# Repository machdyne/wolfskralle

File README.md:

# Wolfskralle Programmer

Wolfskralle is an ISP + spring contact programmer for CH32 MCUs and [Zwölf](https://github.com/machdyne/zwolf) [LS10](https://machdyne.com/product/zwolf-ls10/) modules.

This repo will contain schematics, pinouts and a 3D-printable socket housing for the spring connector.

Find more information on the [Wolfskralle product page](https://machdyne.com/product/wolfskralle-programmer/).

## Pinout

```
7 5 3 1
8 6 4 2
```

| Pin | Signal |
| --- | ------ |
| 1 | ZP1 (Zwölf GSCL) / SWCLK | 
| 3 | ZP2 (Zwölf GSDA) | 
| 5 | SWIO (programmer swio) | 
| 7 | RESET (programmer reset) | 
| 2 | TPWR3V3 (target power) | 
| 4 | TSWIO (target swio) | 
| 6 | TRESET (target reset) | 
| 8 | GND | 

## Firmware

The Wolfskralle's firmware and its command-line tool, `wolfctl`, are being
written in phases; see [docs/plan.md](docs/plan.md) for the plan and the
current state.

```
$ make -C firmware deps && make -C firmware      # firmware/wolfskralle.bin
$ make -C firmware flash                         # with a WCH-LinkE on J2
$ make -C host && make -C host test              # host/wolfctl, protocol tests
$ host/wolfctl info
$ host/wolfctl flash basic-ls10a.bin             # program the module
```

| Document | Contents |
|---|---|
| [docs/plan.md](docs/plan.md) | development plan and history |
| [docs/hardware.md](docs/hardware.md) | the board as the firmware sees it (pins, v0/v1) |
| [docs/firmware.md](docs/firmware.md) | building and flashing the firmware |
| [docs/protocol.md](docs/protocol.md) | the USB protocol |
| [docs/swio.md](docs/swio.md) | the link to the target: SWIO, its timing, the scan |
| [docs/debug.md](docs/debug.md) | connecting to the chip, identifying and reading it |
| [docs/programming.md](docs/programming.md) | programming a module, and the failsafe rules |
| [docs/sechs.md](docs/sechs.md) | checking a module over Sechs: is BASIC installed and running? |
| [docs/wolfctl.md](docs/wolfctl.md) | the command-line tool |
| [docs/hwtest.md](docs/hwtest.md) | hardware tests and their results |

## License

The contents of this repo are released under the [Lone Dynamics Open License](LICENSE.md).

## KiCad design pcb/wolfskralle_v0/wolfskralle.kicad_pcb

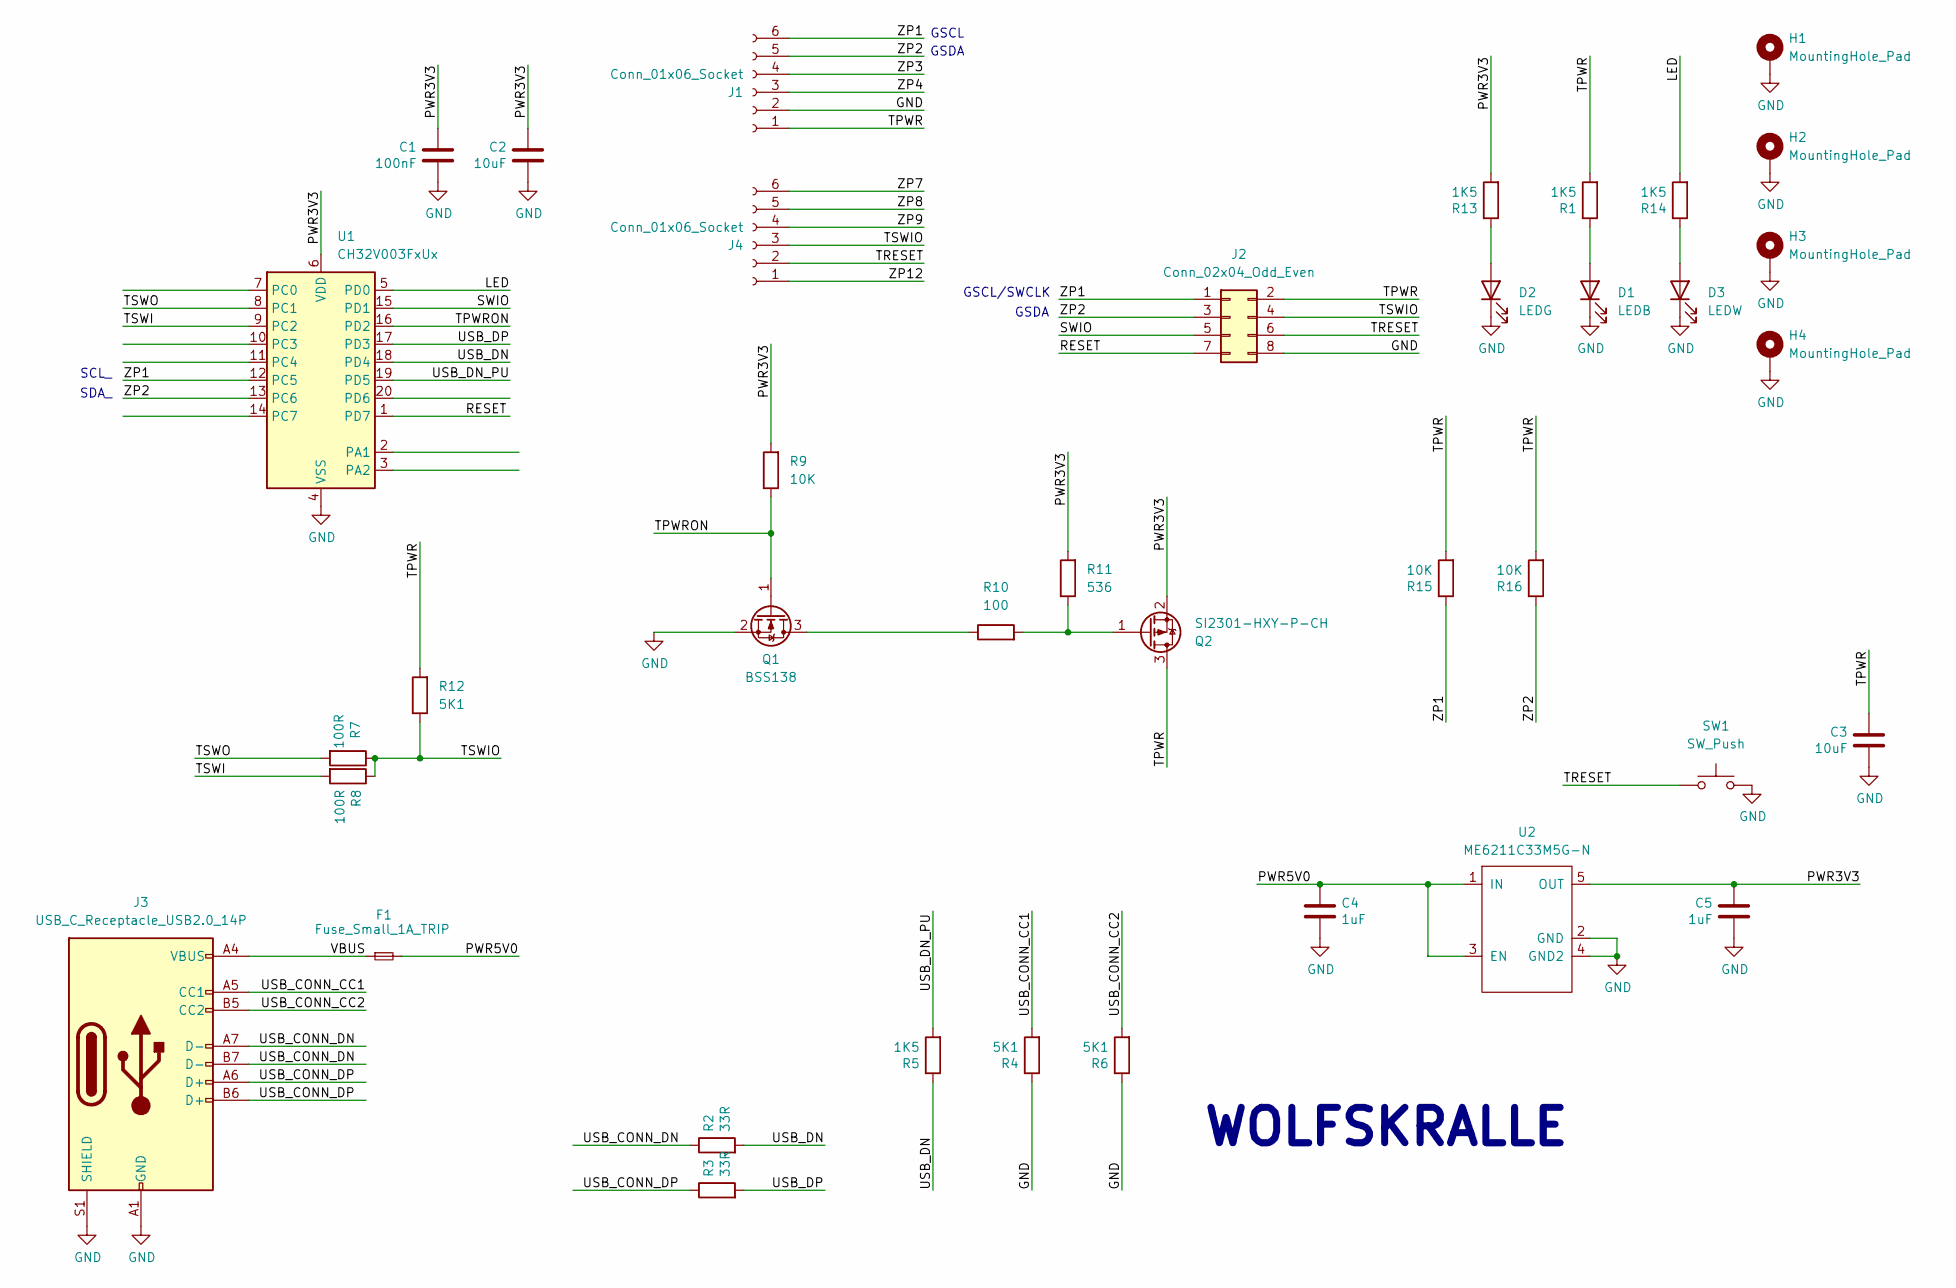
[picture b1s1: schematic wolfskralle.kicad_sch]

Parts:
C1: 100nF; C_0402_1005Metric
C2, C3: 10uF; C_0402_1005Metric
C4, C5: 1uF; C_0402_1005Metric
D1: LEDB; LED_0603_1608Metric
D2: LEDG; LED_0603_1608Metric
D3: LEDW; LED_0603_1608Metric
F1: Fuse_Small_1A_TRIP; Fuse_0603_1608Metric
H1, H2, H3, H4: MountingHole_Pad; MountingHole_2.7mm_M2.5_DIN965_Pad
J1, J4: Conn_01x06_Socket; SPRING-MALE-6P-TIGHTHOLES
J2: Conn_02x04_Odd_Even; PinHeader_2x04_P2.54mm_Horizontal
J3: USB_C_Receptacle_USB2.0_14P; USB_C_Receptacle_HRO_TYPE-C-31-M-12-BIG-PADS-PASTE
Q1: BSS138; SOT-23
Q2: SI2301-HXY-P-CH; SOT-23
R1, R5, R13, R14: 1K5; R_0402_1005Metric
R2, R3: 33R; R_0402_1005Metric
R4, R6, R12: 5K1; R_0402_1005Metric
R7, R8: 100R; R_0402_1005Metric
R9, R15, R16: 10K; R_0402_1005Metric
R10: 100; R_0402_1005Metric
R11: 536; R_0402_1005Metric
SW1: SW_Push; Button_2P_3x4mm
U1: CH32V003FxUx; QFN-20-1EP_3x3mm_P0.4mm_EP1.65x1.65mm
U2: ME6211C33M5G-N; TSOP-5_1.65x3.05mm_P0.95mm

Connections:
/LED: R14.2, U1.5 (PD0)
/PWR3V3: C1.1, C2.1, C5.1, Q2.2 (S), R9.2, R11.2, R13.2, U1.6 (VDD), U2.5 (OUT)
/PWR5V0: C4.1, F1.2, U2.1 (IN), U2.3 (EN)
/RESET: J2.7, U1.1 (PD7)
/SWIO: J2.5, U1.15 (PD1)
/TPWR: C3.1, J1.1, J2.2, Q2.3 (D), R1.2, R12.2, R15.2, R16.2
/TPWRON: Q1.1 (G), R9.1, U1.16 (PD2)
/TRESET: J2.6, J4.2, SW1.1
/TSWI: R8.2, U1.9 (PC2)
/TSWIO: J2.4, J4.3, R7.1, R8.1, R12.1
/TSWO: R7.2, U1.8 (PC1)
/USB_CONN_CC1: J3.A5 (CC1), R4.2
/USB_CONN_CC2: J3.B5 (CC2), R6.2
/USB_CONN_DN: J3.A7 (D-), J3.B7 (D-), R2.1
/USB_CONN_DP: J3.A6 (D+), J3.B6 (D+), R3.1
/USB_DN: R2.2, R5.1, U1.18 (PD4)
/USB_DN_PU: R5.2, U1.19 (PD5)
/USB_DP: R3.2, U1.17 (PD3)
/VBUS: F1.1, J3.A4 (VBUS), J3.A9 (VBUS), J3.B4 (VBUS), J3.B9 (VBUS)
/ZP1: J1.6, J2.1, R15.1, U1.12 (PC5)
/ZP2: J1.5, J2.3, R16.1, U1.13 (PC6)
/ZP3: J1.4
/ZP4: J1.3
/ZP7: J4.6
/ZP8: J4.5
/ZP9: J4.4
/ZP12: J4.1
GND: C1.2, C2.2, C3.2, C4.2, C5.2, D1.1 (K), D2.1 (K), D3.1 (K), H1.1, H2.1, H3.1, H4.1, J1.2, J2.8, J3.A1 (GND), J3.A12 (GND), J3.B1 (GND), J3.B12 (GND), J3.S1 (SHIELD), Q1.2 (S), R4.1, R6.1, SW1.2, U1.4 (VSS), U1.21 (VSS), U2.2 (GND), U2.4 (GND2)
unnamed: D1.2 (A), R1.1
unnamed: D2.2 (A), R13.1
unnamed: D3.2 (A), R14.1
unnamed: Q1.3 (D), R10.1
unnamed: Q2.1 (G), R10.2, R11.1

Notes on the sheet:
GSCL
GSDA
SCL_
GSCL/SWCLK
WOLFSKRALLE
SDA_

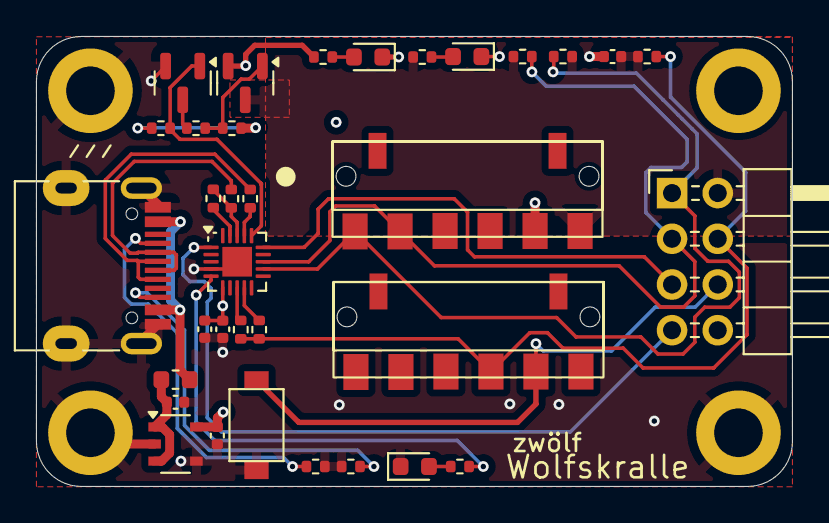
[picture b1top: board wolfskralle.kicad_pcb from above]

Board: 2 copper layers, 42.0 x 25.0 mm, 38 parts (0 on the bottom side), 27 nets.

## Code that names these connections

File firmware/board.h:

/*
 * Wolfskralle board definitions. See docs/hardware.md.
 *
 * Build for v0 (default) or v1:  make BOARD=v1
 */

#ifndef BOARD_H
#define BOARD_H

#include "wkproto.h"

#if defined(BOARD_V1)
#define BOARD_ID        WK_BOARD_V1
#else
#define BOARD_V0        1
#define BOARD_ID        WK_BOARD_V0
/* the watchdog: feeds it (main loop, every SWIO packet, long waits) */
#define WDT_FEED()      (IWDG->CTLR = 0xAAAA)

#endif

#define PIN_LED         PD0     /* white LED D3, high = on */
#define PIN_TPWRON      PD2     /* target power, high = on (R9 pulls it high) */
#define PIN_TSWO        PC1     /* 100R to TSWIO (Zwölf pin 10) */
#define PIN_TSWI        PC2     /* 100R to TSWIO */

/* SWIO uses both, through TIM2 (partial remap 1), whose channels fix the
 * roles; the schematic's names TSWO/TSWI are the other way round, which
 * does not matter, as the two 100R make the network symmetric */
#define PIN_SWIO_OUT    PC2     /* TIM2 CH2: pulses, open drain */
#define PIN_SWIO_IN     PC1     /* TIM2 CH4: input capture */
#define PIN_ZP1         PC5     /* Zwölf pin 1 (A, Sechs SCL), 10K to TPWR */
#define PIN_ZP2         PC6     /* Zwölf pin 2 (B, Sechs SDA), 10K to TPWR */

/* USB (rv003usb): PD3 D+, PD4 D-, PD5 the 1K5 pull-up on D-; usb_config.h */

#if defined(BOARD_V1)
/* v1 connects TRESET (Zwölf pin 11) to the MCU: set the pin here when the
 * v1 schematic is final (PC0, PC3, PC4 or PC7 are free on v0). */
#ifndef PIN_TRESET
#error "BOARD_V1: define PIN_TRESET in board.h"
#endif
#define HAVE_TRESET     1
#else
#define HAVE_TRESET     0       /* v0: TRESET is not connected (hardware bug) */
#endif

#endif

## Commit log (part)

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2025-08-12 add license
2026-03-16 add 3d components
2026-03-16 update hardware notes
